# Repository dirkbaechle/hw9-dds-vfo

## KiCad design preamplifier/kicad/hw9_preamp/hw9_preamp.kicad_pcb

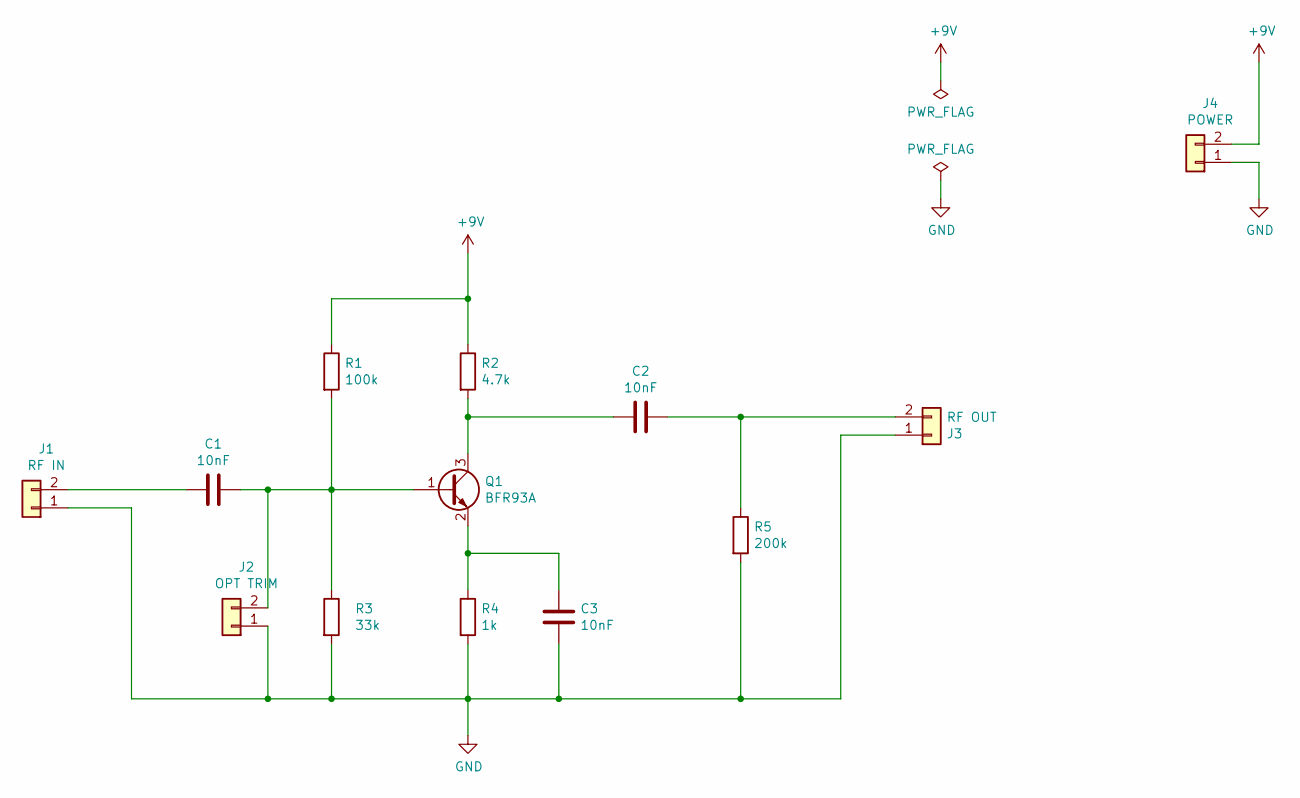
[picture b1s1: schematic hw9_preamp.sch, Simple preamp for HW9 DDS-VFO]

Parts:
C1, C2, C3: 10nF; C_0805_2012Metric
J1: RF IN; Wire_Connector_SMD_01x02
J2: OPT TRIM; R_0805_2012Metric
J3: RF OUT; Wire_Connector_SMD_01x02
J4: POWER; Wire_Connector_SMD_01x02
Q1: BFR93A; SOT-23
R1: 100k; R_0805_2012Metric
R2: 4.7k; R_0805_2012Metric
R3: 33k; R_0805_2012Metric
R4: 1k; R_0805_2012Metric
R5: 200k; R_0805_2012Metric

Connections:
+9V: J4.2, R1.1, R2.1
GND: C3.2, J1.1, J2.1, J3.1, J4.1, R3.2, R4.2, R5.2
unnamed: C1.1, J2.2, Q1.1 (B), R1.2, R3.1
unnamed: C1.2, J1.2
unnamed: C2.1, J3.2, R5.1
unnamed: C2.2, Q1.3 (C), R2.2
unnamed: C3.1, Q1.2 (E), R4.1

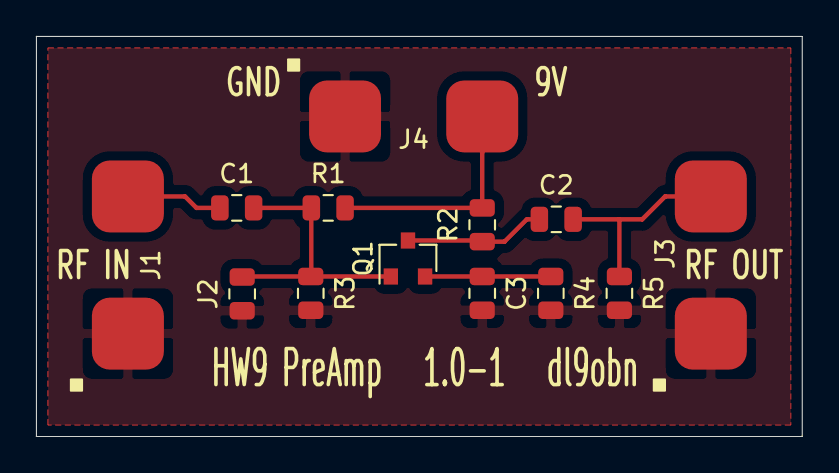
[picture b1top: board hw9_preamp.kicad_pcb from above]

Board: 2 copper layers, 42.5 x 22.2 mm, 13 parts (0 on the bottom side), 7 nets.

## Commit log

2020-01-25 Added original HEX files by DL4JAL, v1.14
2020-01-25 Added original HEX files by DL4JAL, v1.17.
2020-01-25 Added HEX files for UniDDS (QRP Project).
    Added the original firmware for the UniDDS-VFO as used
    by the QRP Project assembly kits. Provided by Nikolai
    Zenker, DL7NIK.
2020-01-26 Added original ASM source and new bandswitch.
    Added the PDF with the original ASM source code and
    an updated HEX file for the bandswitch PIC.
2020-01-27 Converted PDF to a plain ASM file.
    With the help of pdftotext and a simple Python2 script,
    I was able to extract plain ASM text from the 'avfo.pdf'
    file in v1.08.
2020-01-27 Disassembled UniDDS HEX files.
    We disassembled the original HEX files for the UniDDS-VFO
    (as provided by the QRP Project, Nikolai Zenker, DL7NIK).
    Then we also resynthesized them by sending them through
    'gpasm' again, to ensure that we're able to recreate the
    original HEX files from scratch.
    Like this, we have a complete toolchain for the development
2020-07-05 Added support for disassembly w labels.
2020-10-30 Added original source for Uni-DDS-VFO.
    Added the original PIC source files as provided
    by Andreas Lingnau (DF4JAL).
2021-01-10 Removed t2mSek function.
    Like this, the resulting ASM/HEX file is as close as possible
    to the code used in v1.10 of the Uni-DDS.
2021-01-10 Added noweb file for mc.pic.
    This noweb file creates a verbatim copy of the original mc.pic (see
    qrp_projects/original_sources).
    It will be the new basis for all our upcoming changes in order to
    properly support the HW9.
2021-09-23 Added basic mplab project for re-programming PIC.
    The project configured is set up to use absolute mode, such
    that the ASM file (as compiled from the uni-dds-hw9.nw)
    can be compiled successfully.
    Relocatable mode doesn't work, due to the endpage
    chack embedded in the code...
2021-09-23 Added v1.0-1 of the HW9 pre-amplifier.
2021-10-02 Changed language to German for Noweb.
